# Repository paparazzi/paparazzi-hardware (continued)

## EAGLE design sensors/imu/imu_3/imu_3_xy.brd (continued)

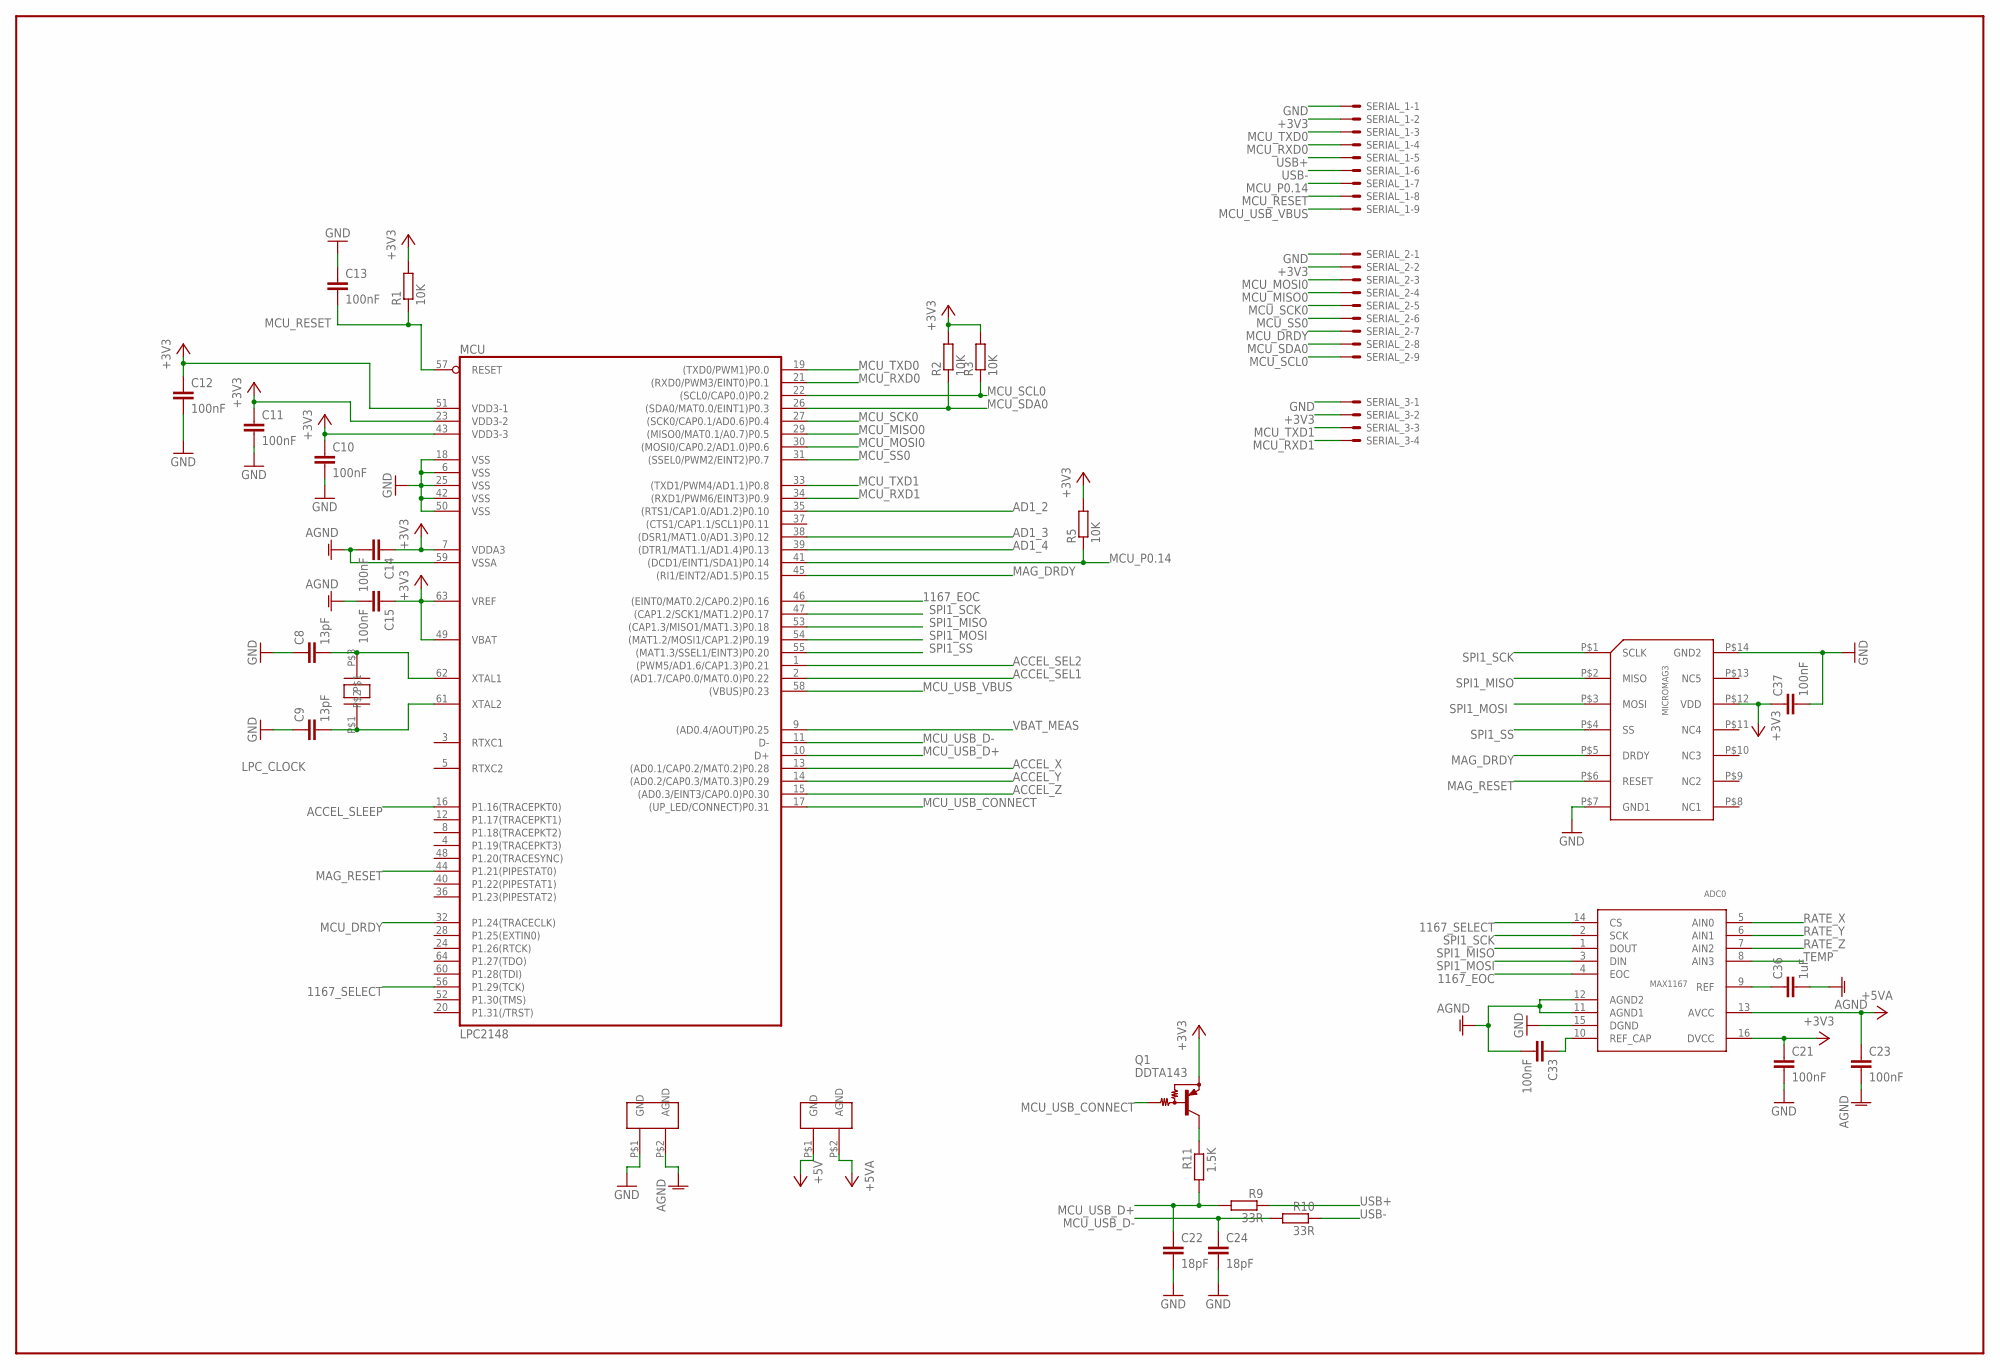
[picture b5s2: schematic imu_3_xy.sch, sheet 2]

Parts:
ADC0: MAX1167; QSOP16
C8, C9: 13pF; C0402K
C10, C11, C12, C13, C14, C15, C21, C23, C33, C37: 100nF; C0402K
C22, C24: 18pF; C0402K
C36: 1uF; C0805
CRYSTAL1: 14.764Mhz; CTS_CRYSTAL
MCU: LPC2148; SQFP-S-10X10-64
Q1: DDTA143; SC59-BEC
R1, R2, R3, R5: 10K; R0402
R9, R10: 33R; R1005
R11: 1.5K; R1005
SERIAL_1, SERIAL_2: 53048-09
SERIAL_3: 53048-04
U$9: MICROMAG3
U$11, U$21: TEST_CON_GP

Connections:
1167_EOC: ADC0.4 (EOC), MCU.46 ((EINT0/MAT0.2/CAP0.2)P0.16)
1167_SELECT: ADC0.14 (CS), MCU.56 (P1.29(TCK))
+3V3: ADC0.16 (DVCC), C10.1, C11.1, C12.1, C14.1, C15.1, C21.1, C37.1, MCU.7 (VDDA3), MCU.23 (VDD3-2), MCU.43 (VDD3-3), MCU.49 (VBAT), MCU.51 (VDD3-1), MCU.63 (VREF), Q1.E, R1.2, R2.2, R3.2, R5.2, SERIAL_1.2, SERIAL_2.2, SERIAL_3.2, U$9.P$12 (VDD); also elsewhere on the board
+5V: U$21.P$1 (GND); also elsewhere on the board
+5VA: ADC0.13 (AVCC), C23.1, U$21.P$2 (AGND); also elsewhere on the board
ACCEL_SEL1: MCU.2 ((AD1.7/CAP0.0/MAT0.0)P0.22); also elsewhere on the board
ACCEL_SEL2: MCU.1 ((PWM5/AD1.6/CAP1.3)P0.21); also elsewhere on the board
ACCEL_SLEEP: MCU.16 (P1.16(TRACEPKT0)); also elsewhere on the board
ACCEL_X: MCU.13 ((AD0.1/CAP0.2/MAT0.2)P0.28); also elsewhere on the board
ACCEL_Y: MCU.14 ((AD0.2/CAP0.3/MAT0.3)P0.29); also elsewhere on the board
ACCEL_Z: MCU.15 ((AD0.3/EINT3/CAP0.0)P0.30); also elsewhere on the board
AD1_2: MCU.35 ((RTS1/CAP1.0/AD1.2)P0.10)
AD1_3: MCU.38 ((DSR1/MAT1.0/AD1.3)P0.12)
AD1_4: MCU.39 ((DTR1/MAT1.1/AD1.4)P0.13)
AGND: ADC0.11 (AGND1), ADC0.12 (AGND2), C14.2, C15.2, C23.2, C33.2, C36.2, MCU.59 (VSSA), U$11.P$2 (AGND); also elsewhere on the board
GND: ADC0.15 (DGND), C8.1, C9.1, C10.2, C11.2, C12.2, C13.1, C21.2, C22.2, C24.2, C37.2, MCU.6 (VSS), MCU.18 (VSS), MCU.25 (VSS), MCU.42 (VSS), MCU.50 (VSS), SERIAL_1.1, SERIAL_2.1, SERIAL_3.1, U$9.P$7 (GND1), U$9.P$14 (GND2), U$11.P$1 (GND); also elsewhere on the board
LPC_CLOCK: C9.2, CRYSTAL1.P$1, MCU.61 (XTAL2)
MAG_DRDY: MCU.45 ((RI1/EINT2/AD1.5)P0.15), U$9.P$5 (DRDY)
MAG_RESET: MCU.44 (P1.21(PIPESTAT0)), U$9.P$6 (RESET)
MCU_DRDY: MCU.32 (P1.24(TRACECLK)), SERIAL_2.7
MCU_MISO0: MCU.29 ((MISO0/MAT0.1/A0.7)P0.5), SERIAL_2.4
MCU_MOSI0: MCU.30 ((MOSI0/CAP0.2/AD1.0)P0.6), SERIAL_2.3
MCU_P0.14: MCU.41 ((DCD1/EINT1/SDA1)P0.14), R5.1, SERIAL_1.7
MCU_RESET: C13.2, MCU.57 (RESET), R1.1, SERIAL_1.8
MCU_RXD0: MCU.21 ((RXD0/PWM3/EINT0)P0.1), SERIAL_1.4
MCU_RXD1: MCU.34 ((RXD1/PWM6/EINT3)P0.9), SERIAL_3.4
MCU_SCK0: MCU.27 ((SCK0/CAP0.1/AD0.6)P0.4), SERIAL_2.5
MCU_SCL0: MCU.22 ((SCL0/CAP0.0)P0.2), R3.1, SERIAL_2.9
MCU_SDA0: MCU.26 ((SDA0/MAT0.0/EINT1)P0.3), R2.1, SERIAL_2.8
MCU_SS0: MCU.31 ((SSEL0/PWM2/EINT2)P0.7), SERIAL_2.6
MCU_TXD0: MCU.19 ((TXD0/PWM1)P0.0), SERIAL_1.3
MCU_TXD1: MCU.33 ((TXD1/PWM4/AD1.1)P0.8), SERIAL_3.3
MCU_USB_CONNECT: MCU.17 ((UP_LED/CONNECT)P0.31), Q1.B
MCU_USB_D+: C22.1, MCU.10 (D+), R9.2, R11.2
MCU_USB_D-: C24.1, MCU.11 (D-), R10.2
MCU_USB_VBUS: MCU.58 ((VBUS)P0.23), SERIAL_1.9
unnamed: C8.2, CRYSTAL1.P$3, MCU.62 (XTAL1)
unnamed: Q1.C, R11.1
unnamed: ADC0.10 (REF_CAP), C33.1
unnamed: ADC0.9 (REF), C36.1
RATE_X: ADC0.5 (AIN0); also elsewhere on the board
RATE_Y: ADC0.6 (AIN1); also elsewhere on the board
RATE_Z: ADC0.7 (AIN2); also elsewhere on the board
SPI1_MISO: ADC0.1 (DOUT), MCU.53 ((CAP1.3/MISO1/MAT1.3)P0.18), U$9.P$2 (MISO)
SPI1_MOSI: ADC0.3 (DIN), MCU.54 ((MAT1.2/MOSI1/CAP1.2)P0.19), U$9.P$3 (MOSI)
SPI1_SCK: ADC0.2 (SCK), MCU.47 ((CAP1.2/SCK1/MAT1.2)P0.17), U$9.P$1 (SCLK)
SPI1_SS: MCU.55 ((MAT1.3/SSEL1/EINT3)P0.20), U$9.P$4 (SS)
TEMP: ADC0.8 (AIN3); also elsewhere on the board
USB+: R9.1, SERIAL_1.5
USB-: R10.1, SERIAL_1.6
VBAT_MEAS: MCU.9 ((AD0.4/AOUT)P0.25); also elsewhere on the board

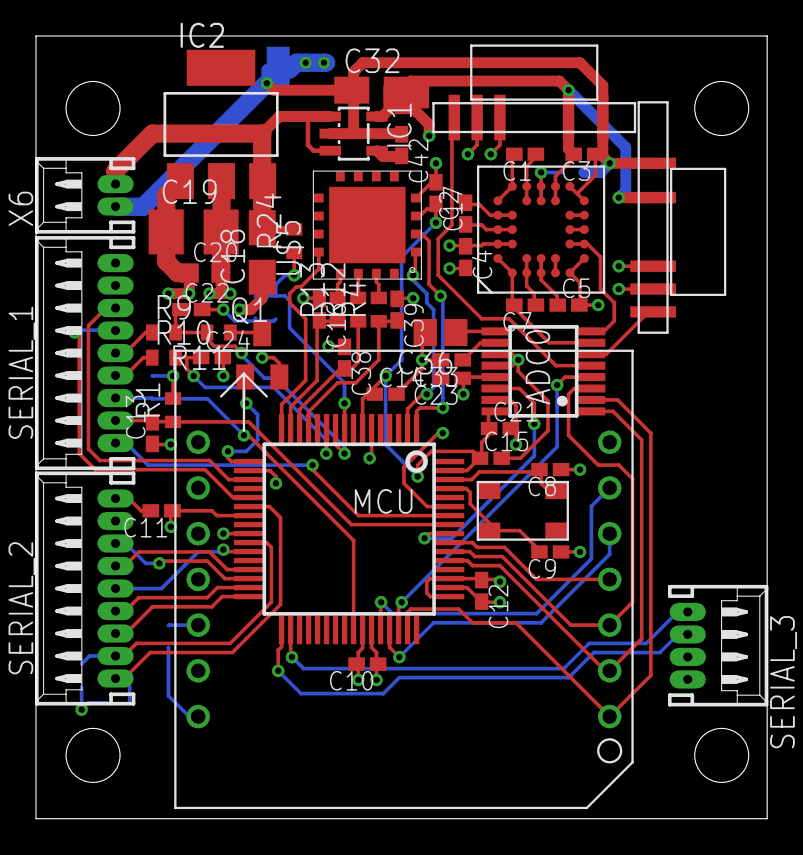
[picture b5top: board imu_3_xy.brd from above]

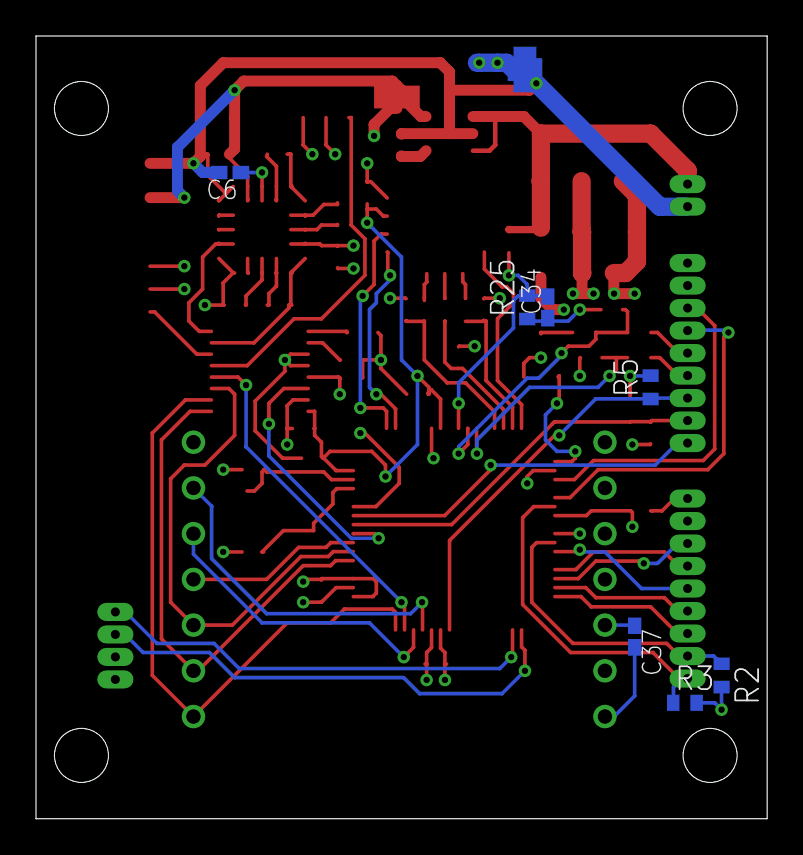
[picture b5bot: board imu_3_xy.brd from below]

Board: 4 copper layers, 40.6 x 43.5 mm, 61 parts (8 on the bottom side), 63 nets.

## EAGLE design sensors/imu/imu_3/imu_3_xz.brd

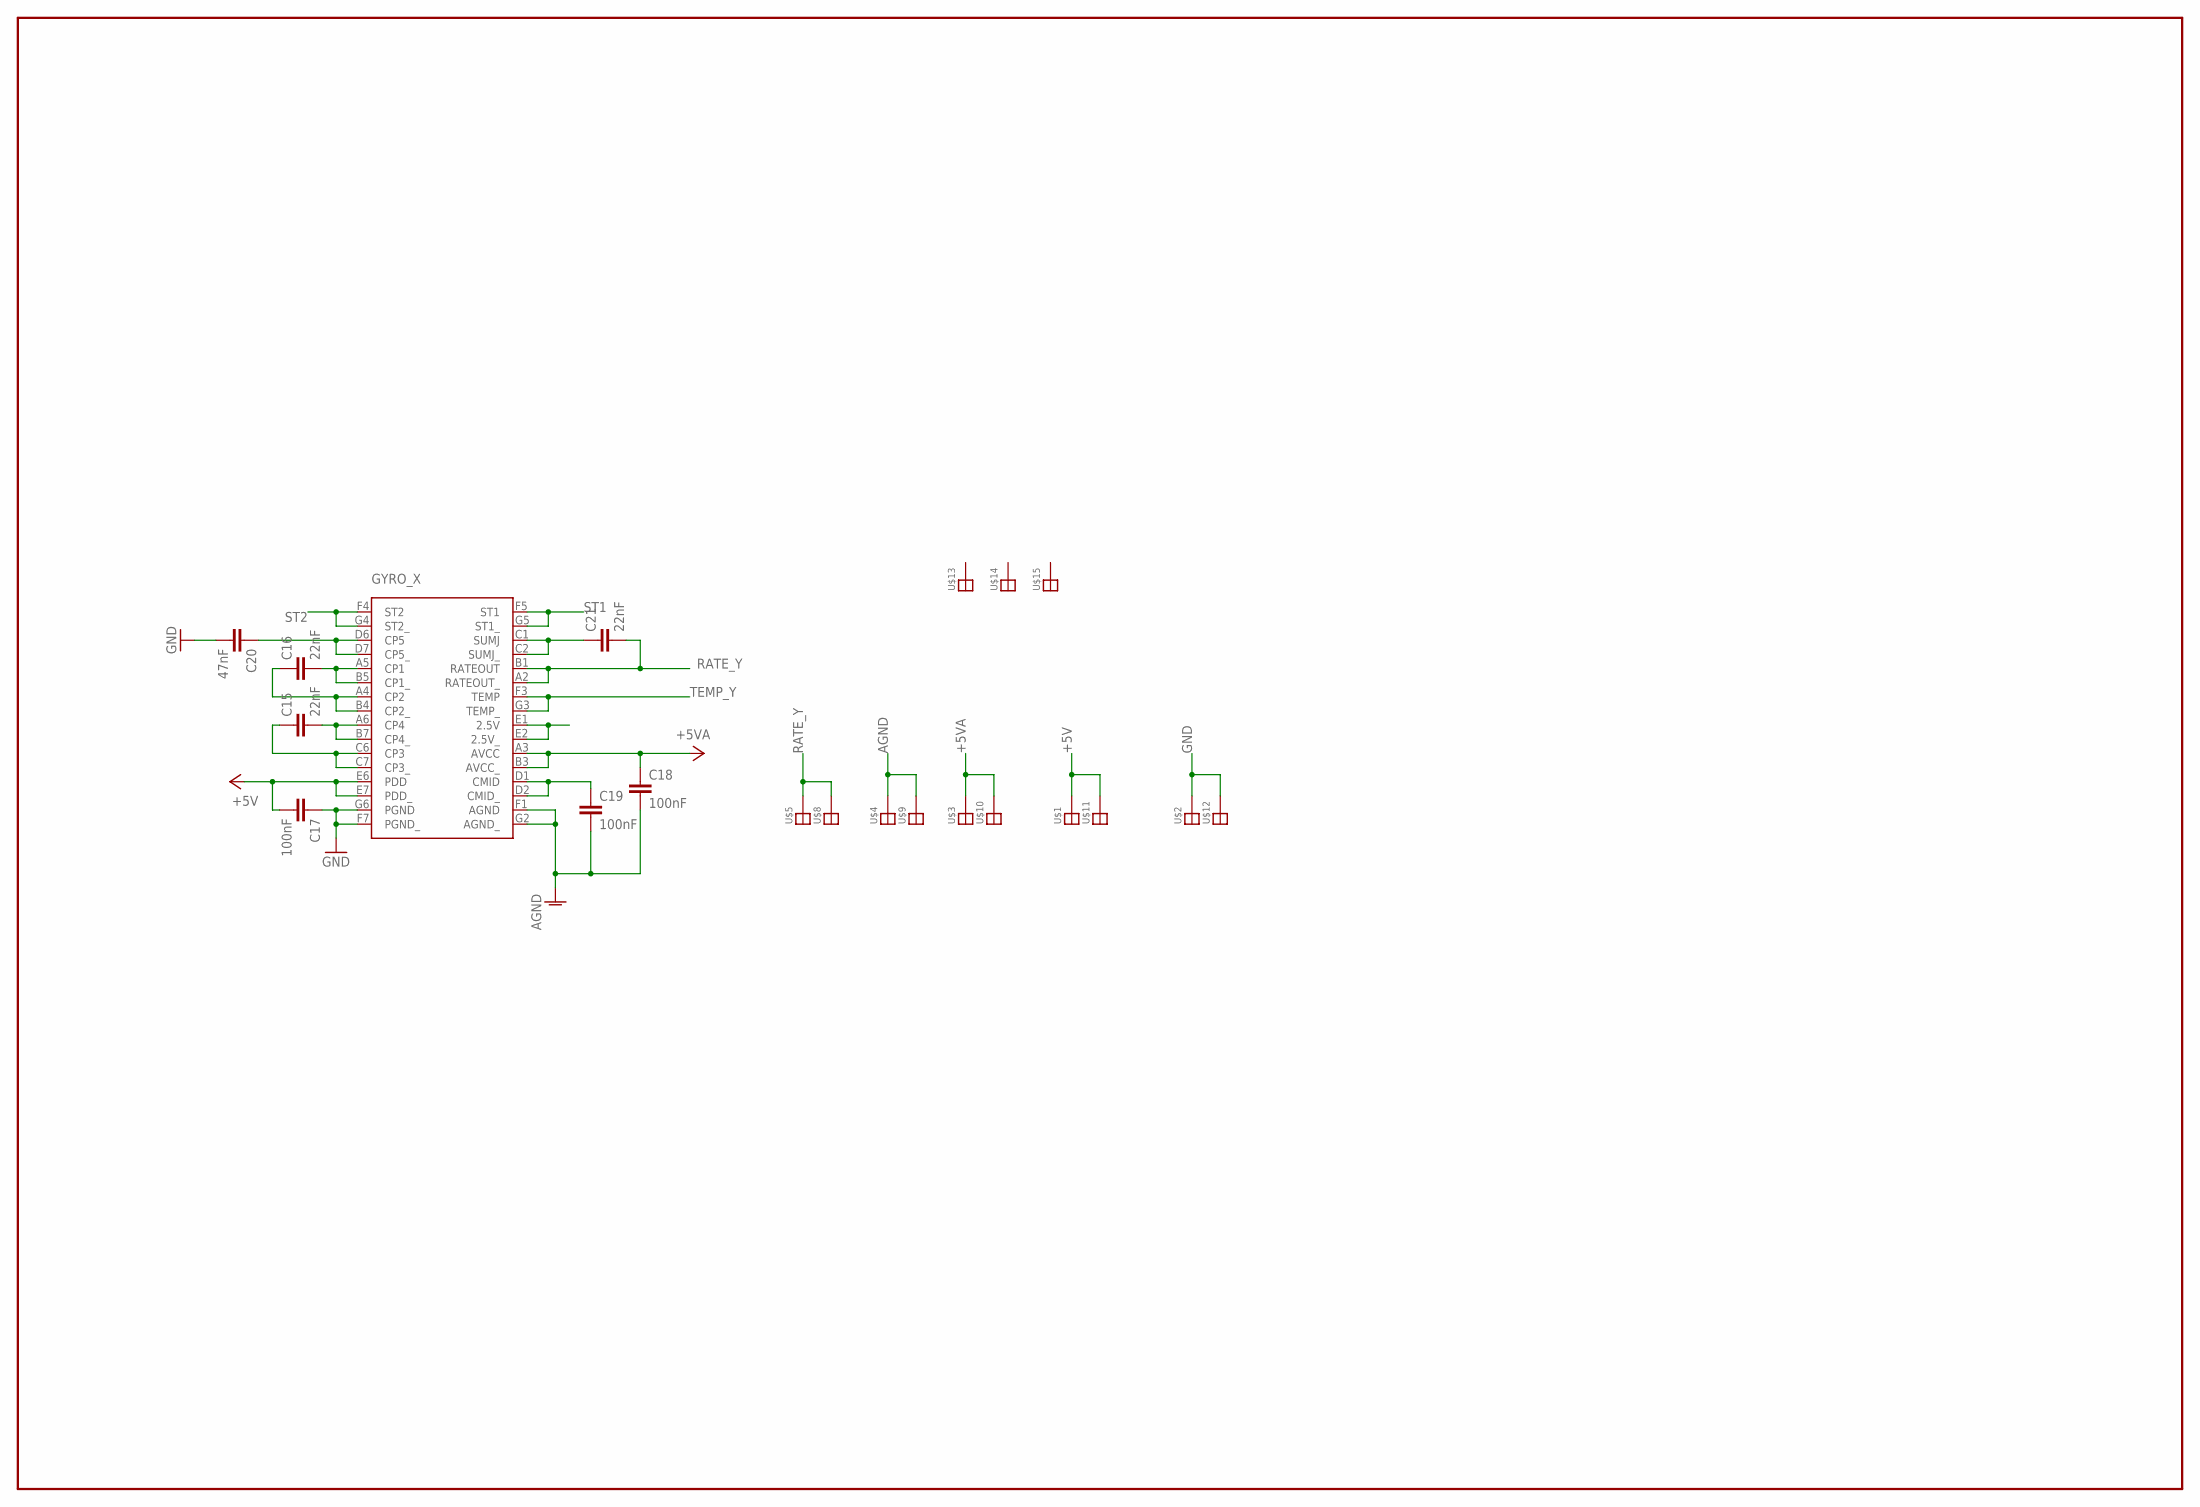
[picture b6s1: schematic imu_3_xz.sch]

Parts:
C15, C16, C21: 22nF; C0402K
C17, C18, C19: 100nF; C0402K
C20: 47nF; C0402K
GYRO_X: ADXR; BC-32
U$1, U$2, U$3, U$4, U$5, U$8, U$9, U$10, U$11, U$12, U$13, U$14, U$15: SOLDER_PAD

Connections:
+5V: C17.2, GYRO_X.E6 (PDD), GYRO_X.E7 (PDD_), U$1.P$1, U$11.P$1
+5VA: C18.1, GYRO_X.A3 (AVCC), GYRO_X.B3 (AVCC_), U$3.P$1, U$10.P$1
AGND: C18.2, C19.2, GYRO_X.F1 (AGND), GYRO_X.G2 (AGND_), U$4.P$1, U$9.P$1
GND: C17.1, C20.2, GYRO_X.F7 (PGND_), GYRO_X.G6 (PGND), U$2.P$1, U$12.P$1
unnamed: C21.1, GYRO_X.C1 (SUMJ), GYRO_X.C2 (SUMJ_)
unnamed: C15.1, GYRO_X.C6 (CP3), GYRO_X.C7 (CP3_)
unnamed: C20.1, GYRO_X.D6 (CP5), GYRO_X.D7 (CP5_)
unnamed: C16.2, GYRO_X.A5 (CP1), GYRO_X.B5 (CP1_)
unnamed: C16.1, GYRO_X.A4 (CP2), GYRO_X.B4 (CP2_)
unnamed: C15.2, GYRO_X.A6 (CP4), GYRO_X.B7 (CP4_)
unnamed: GYRO_X.E1 (2.5V), GYRO_X.E2 (2.5V_)
unnamed: C19.1, GYRO_X.D1 (CMID), GYRO_X.D2 (CMID_)
RATE_Y: C21.2, GYRO_X.A2 (RATEOUT_), GYRO_X.B1 (RATEOUT), U$5.P$1, U$8.P$1
ST1: GYRO_X.F5 (ST1), GYRO_X.G5 (ST1_)
ST2: GYRO_X.F4 (ST2), GYRO_X.G4 (ST2_)
TEMP_Y: GYRO_X.F3 (TEMP), GYRO_X.G3 (TEMP_)

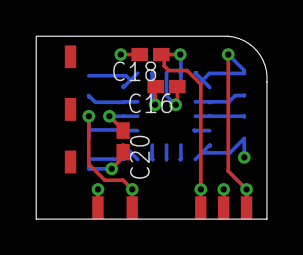
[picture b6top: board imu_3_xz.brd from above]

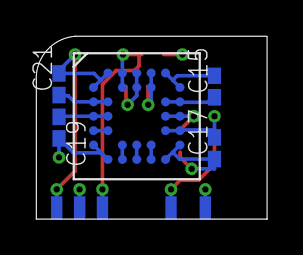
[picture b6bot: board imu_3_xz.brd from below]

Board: 4 copper layers, 12.8 x 10.2 mm, 21 parts (10 on the bottom side), 16 nets.
